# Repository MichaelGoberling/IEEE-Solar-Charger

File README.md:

# IEEE-Solar-Charger

This repository holds the board information for a solar charger IC that uses the TPS63061 as a buck boost converter. This IC takes and input from 4.5 to 6.5 volts and converts it to a steady 5V 800mA output. 

Check out sch.png to see the schematic and brd.png to see the board.

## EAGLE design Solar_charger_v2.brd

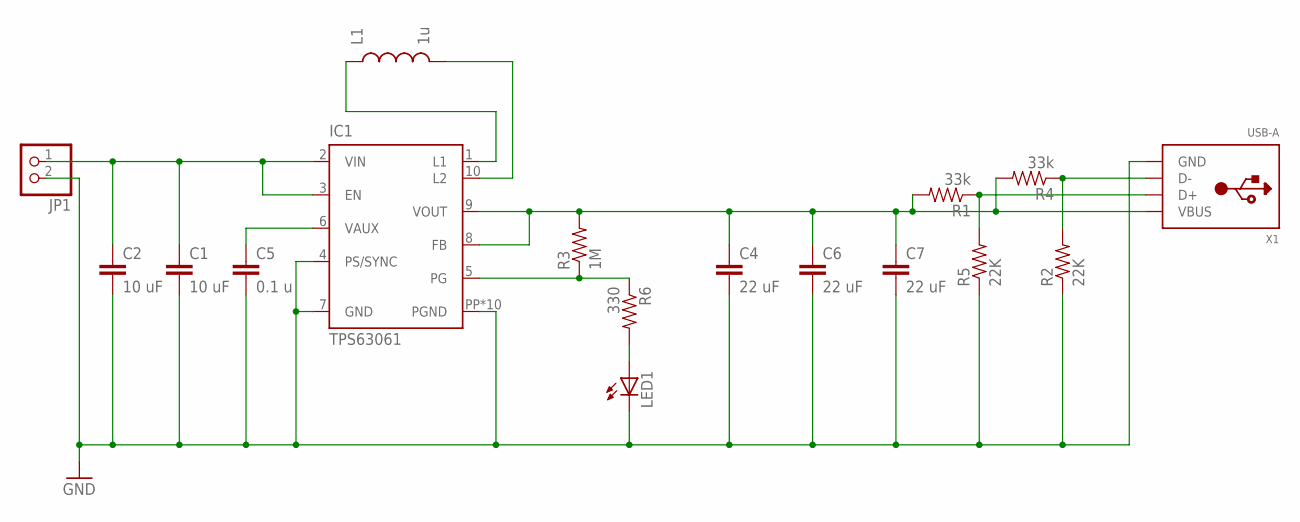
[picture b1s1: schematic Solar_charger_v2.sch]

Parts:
C1, C2: 10 uF; 1206
C4, C6, C7: 22 uF; 1206
C5: 0.1 u; 1206
IC1: TPS63061; DSC-S-PWSON-N10
JP1: JST_2PIN-SMT; JST-PH-2-SMT
L1: 1u; 1210
LED1: LEDSML0805; SML0805
R1, R4: 33k; 1206
R2, R5: 22K; 1206
R3: 1M; 1206
R6: 330; 1206
X1: USB-A; MOLEX_480371000

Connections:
GND: C1.2, C2.2, C4.2, C5.2, C6.2, C7.2, IC1.4 (PS/SYNC), IC1.7 (GND), IC1.PP (PGND), IC1.PP@1 (PGND), IC1.PP@2 (PGND), IC1.PP@3 (PGND), IC1.PP@4 (PGND), IC1.PP@5 (PGND), IC1.PP@7 (PGND), IC1.PP@8 (PGND), IC1.PP@9 (PGND), IC1.PP@10 (PGND), JP1.2 (1), LED1.C, R2.1, R5.1, X1.4 (GND)
unnamed: IC1.10 (L2), L1.2
unnamed: IC1.1 (L1), L1.1
unnamed: IC1.5 (PG), R3.1, R6.1
unnamed: C5.1, IC1.6 (VAUX)
unnamed: R2.2, R4.1, X1.2 (D-)
unnamed: LED1.A, R6.2
unnamed: R1.1, R5.2, X1.3 (D+)
VIN: C1.1, C2.1, IC1.2 (VIN), IC1.3 (EN), JP1.1 (2)
VOUT: C4.1, C6.1, C7.1, IC1.8 (FB), IC1.9 (VOUT), R1.2, R3.2, R4.2, X1.1 (VBUS)

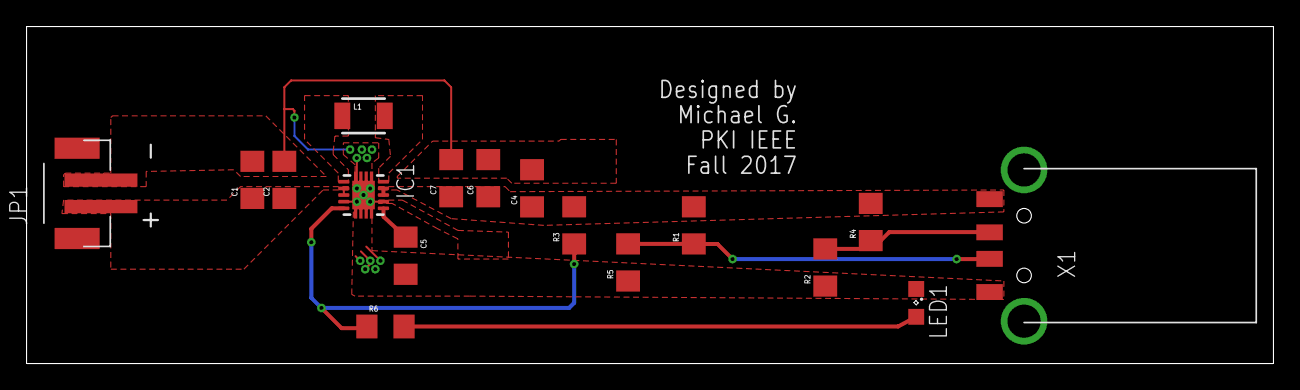
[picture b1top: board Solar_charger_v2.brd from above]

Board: 2 copper layers, 94.0 x 25.4 mm, 17 parts (0 on the bottom side), 10 nets.

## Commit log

2018-03-01 Final Commit

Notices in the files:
parts and their libraries:
SparkFun-Passives: Licensing: Creative Commons ShareAlike 4.0 International - https://creativecommons.org/licenses/by-sa/4.0
